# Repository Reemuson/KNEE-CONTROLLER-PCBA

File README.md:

# Boardwright Preview Outputs

Generated from `a710bf6fdfe838f620b5ccc1c5d6b80bbb2f2a4c` on branch `dev`.

Variant: `PRELIMINARY`

This branch is disposable and generated by GitHub Actions. Do not edit
files here by hand.

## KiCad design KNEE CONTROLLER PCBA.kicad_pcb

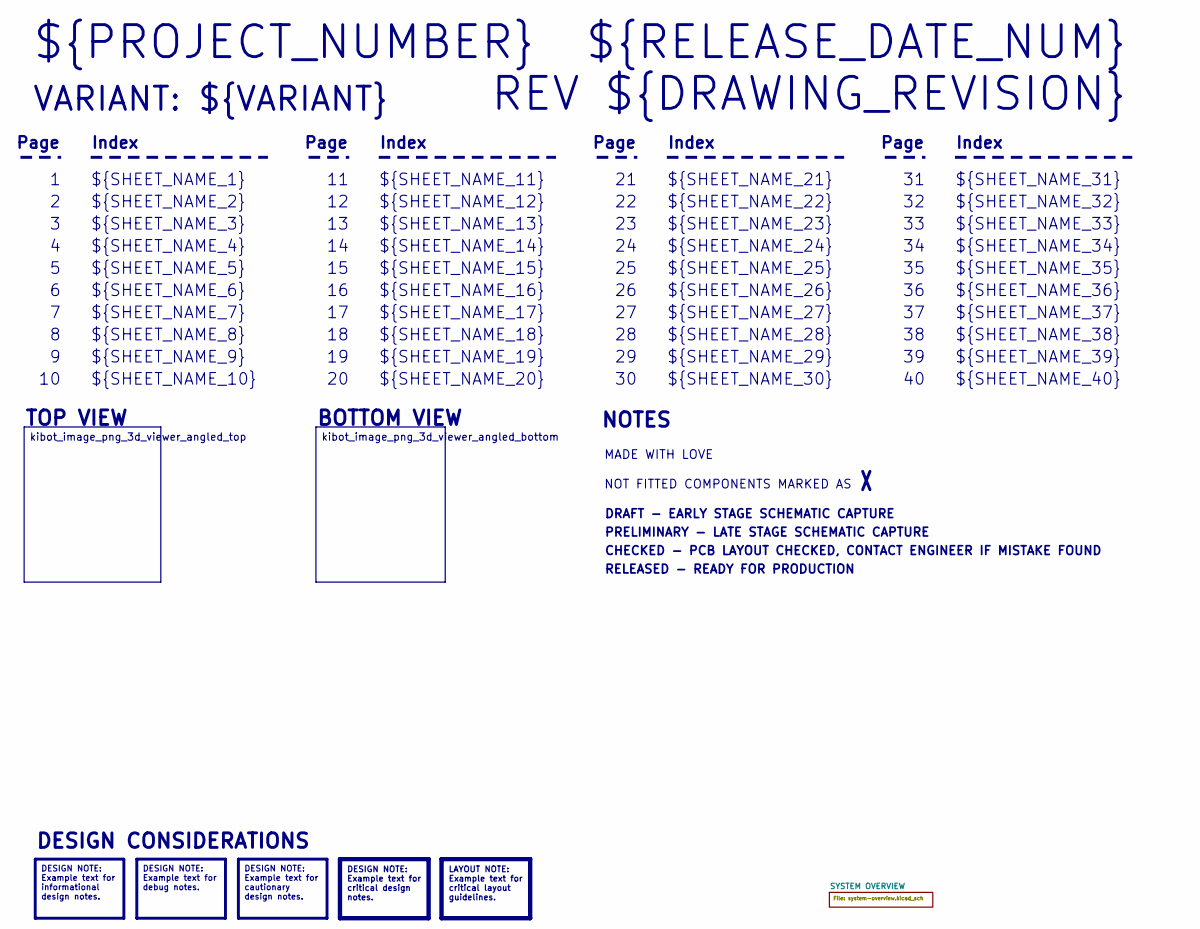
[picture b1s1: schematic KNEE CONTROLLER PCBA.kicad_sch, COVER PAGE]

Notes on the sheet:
VARIANT: ${VARIANT}
RELEASED - READY FOR PRODUCTION
${SHEET_NAME_24}
Index
Page
PRELIMINARY - LATE STAGE SCHEMATIC CAPTURE
${SHEET_NAME_22}
DRAFT - EARLY STAGE SCHEMATIC CAPTURE
${SHEET_NAME_12}
${SHEET_NAME_8}
${SHEET_NAME_2}
${SHEET_NAME_5}
${SHEET_NAME_20}
${SHEET_NAME_23}
${RELEASE_DATE_NUM}
${SHEET_NAME_35}
NOT FITTED COMPONENTS MARKED AS
${SHEET_NAME_11}
${SHEET_NAME_6}
${SHEET_NAME_37}
${SHEET_NAME_26}
${SHEET_NAME_36}
REV ${DRAWING_REVISION}
${SHEET_NAME_15}
CHECKED - PCB LAYOUT CHECKED, CONTACT ENGINEER IF MISTAKE FOUND
BOTTOM VIEW
${SHEET_NAME_14}
${SHEET_NAME_21}
${SHEET_NAME_17}
${SHEET_NAME_18}
${SHEET_NAME_7}
${SHEET_NAME_31}
${PROJECT_NUMBER}
NOTES
${SHEET_NAME_40}
${SHEET_NAME_39}
${SHEET_NAME_32}
${SHEET_NAME_1}
${SHEET_NAME_9}
${SHEET_NAME_38}

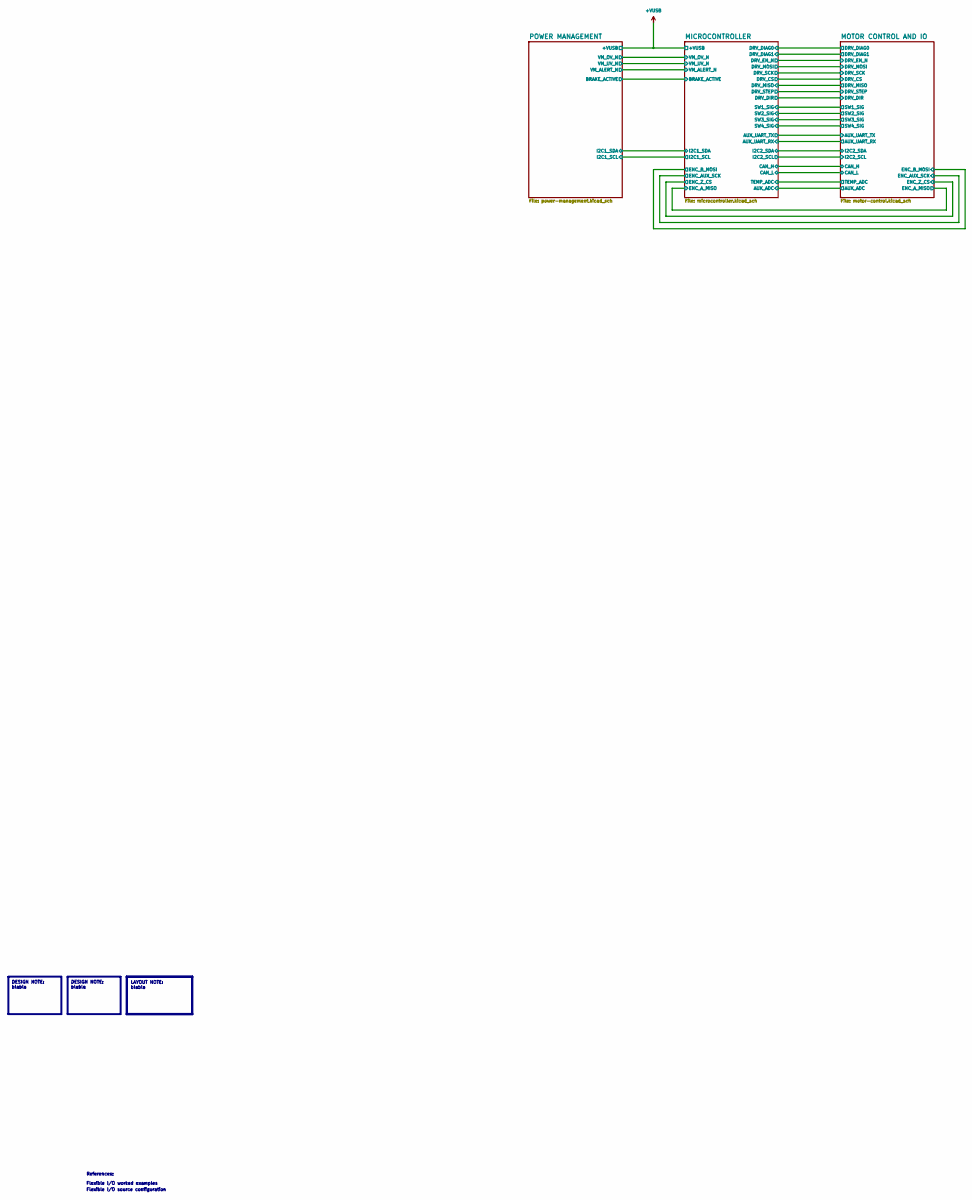
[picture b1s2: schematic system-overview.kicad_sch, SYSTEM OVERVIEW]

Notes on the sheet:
References:
Flexible I/O worked examples
Flexible I/O source configuration
DESIGN NOTE: blabla
LAYOUT NOTE: blabla

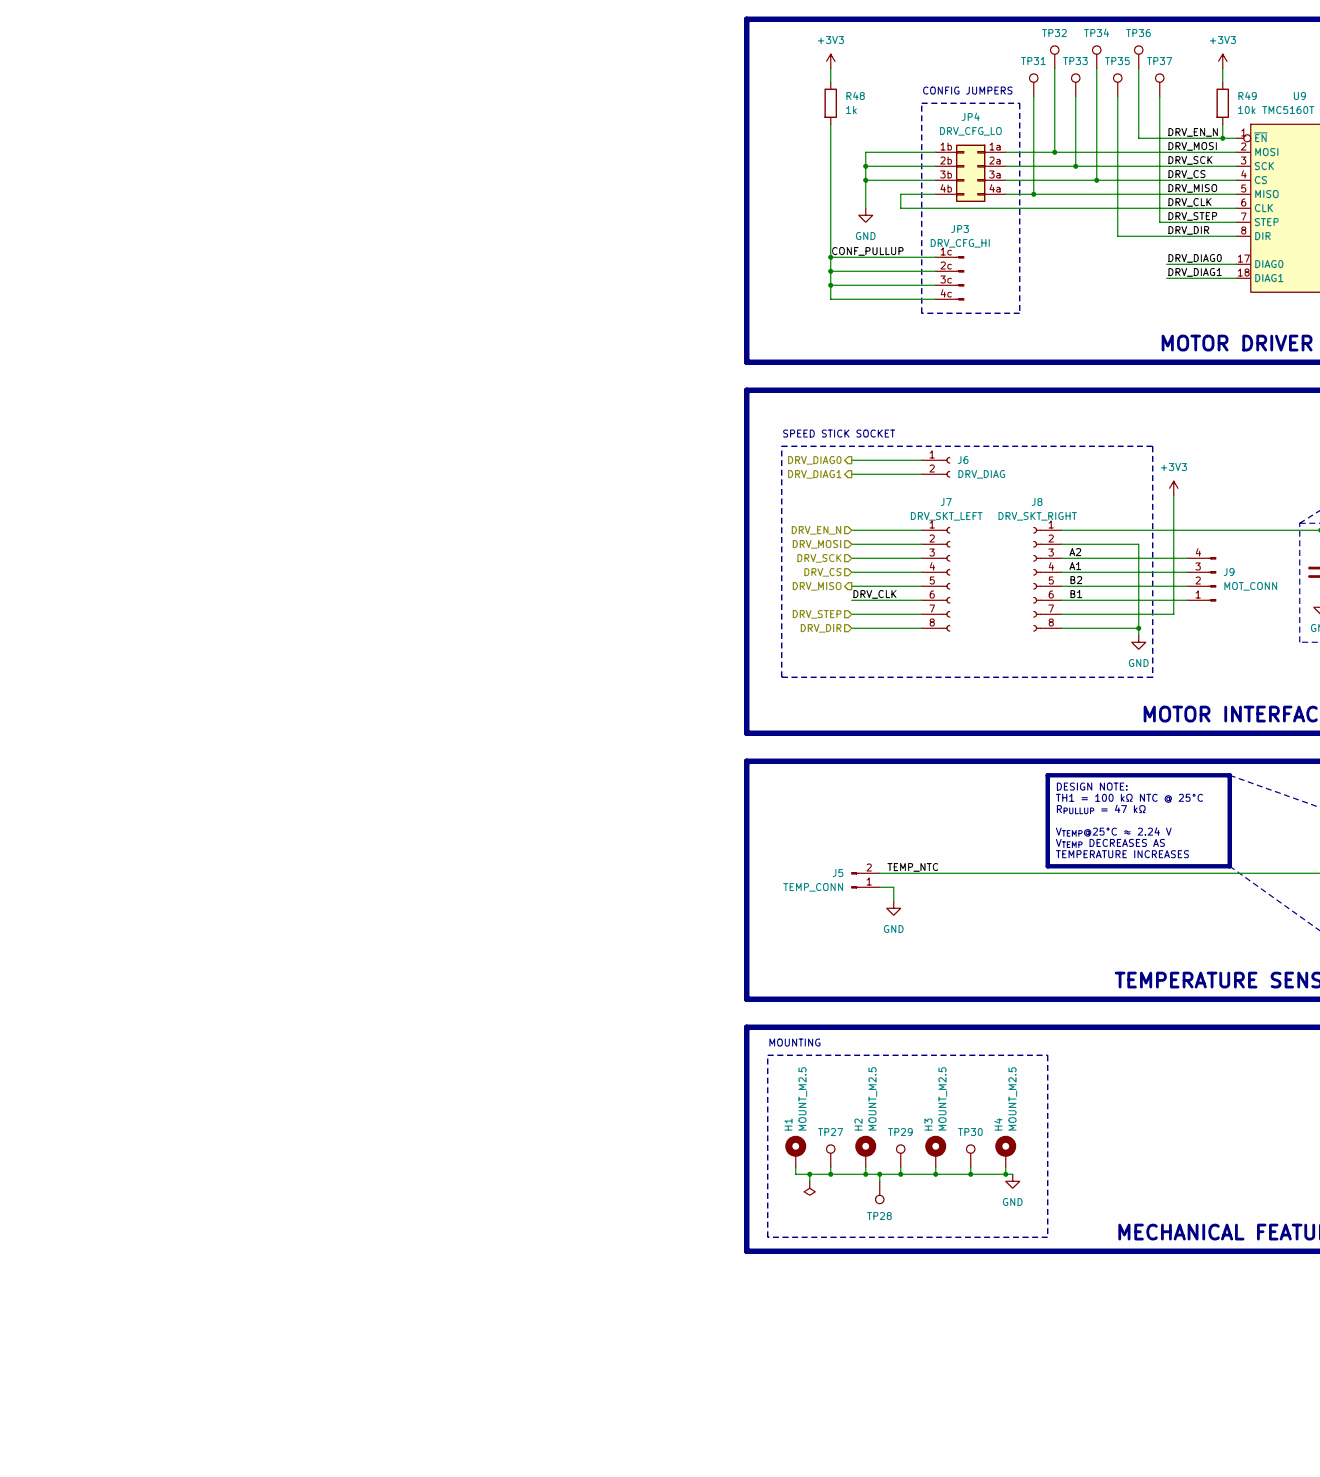
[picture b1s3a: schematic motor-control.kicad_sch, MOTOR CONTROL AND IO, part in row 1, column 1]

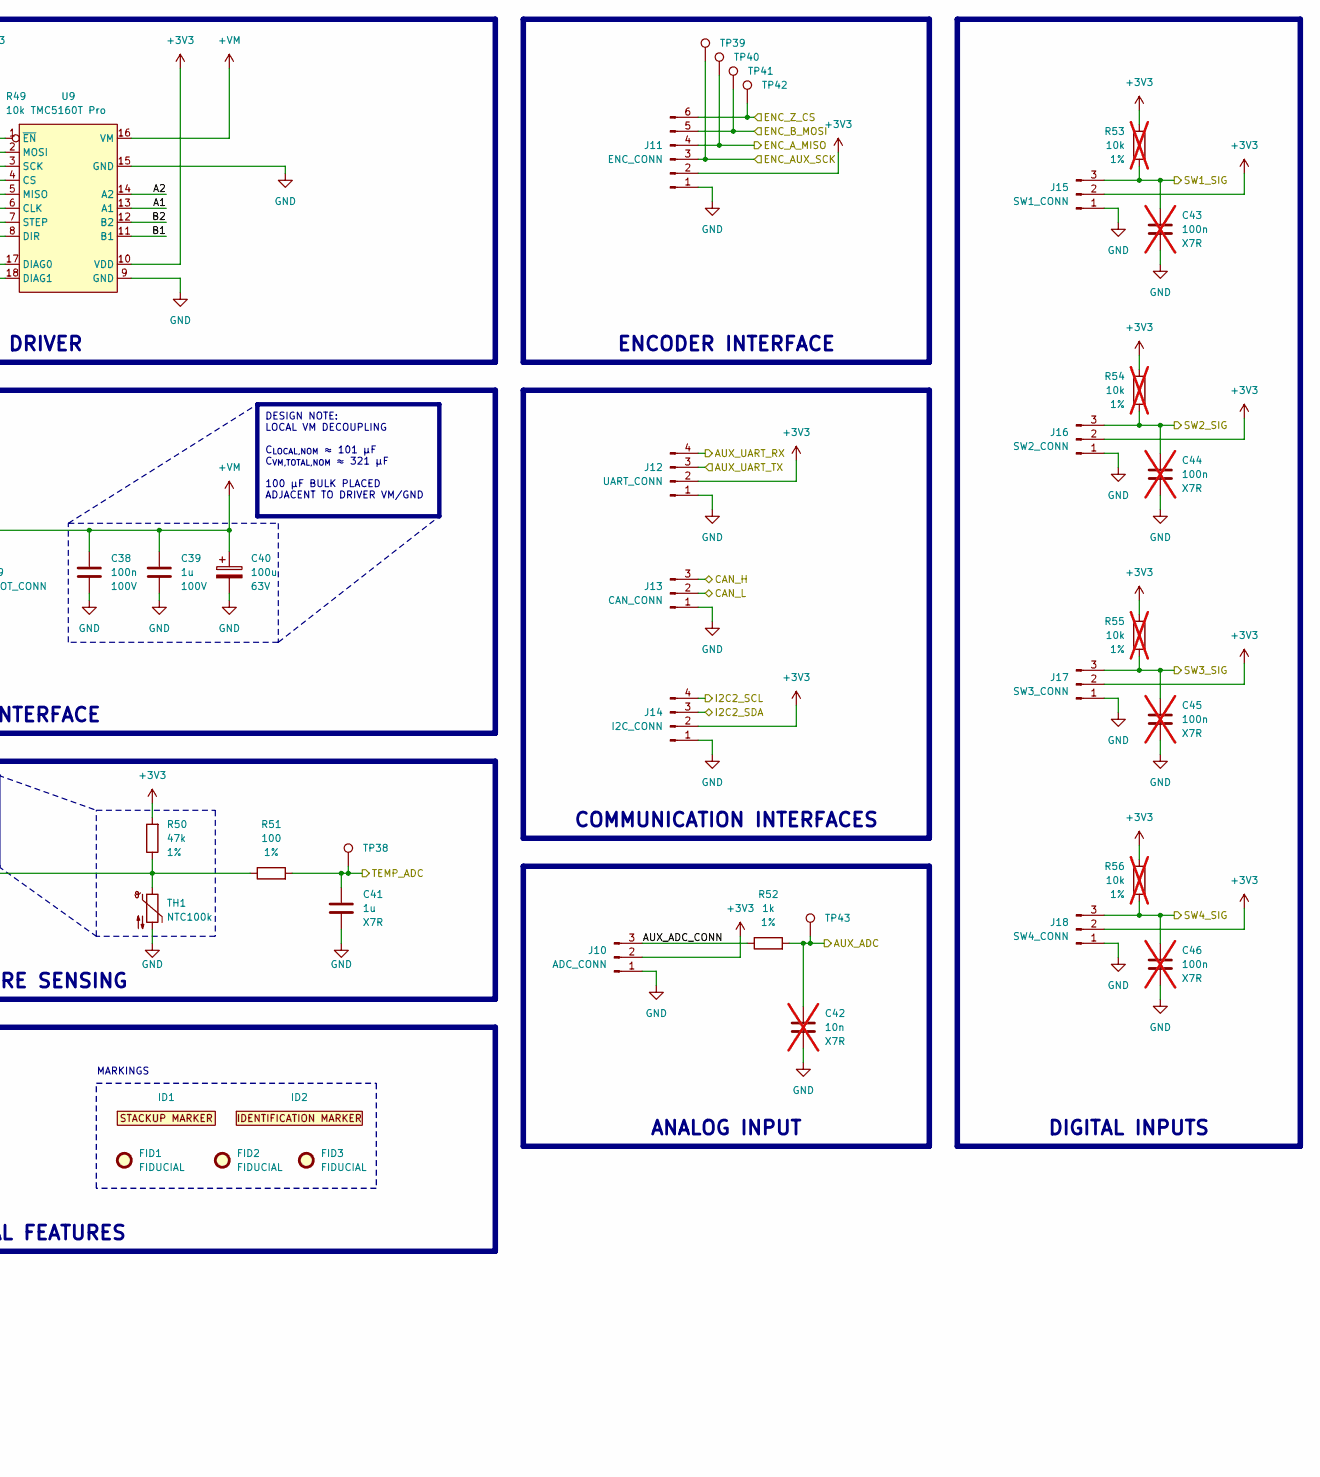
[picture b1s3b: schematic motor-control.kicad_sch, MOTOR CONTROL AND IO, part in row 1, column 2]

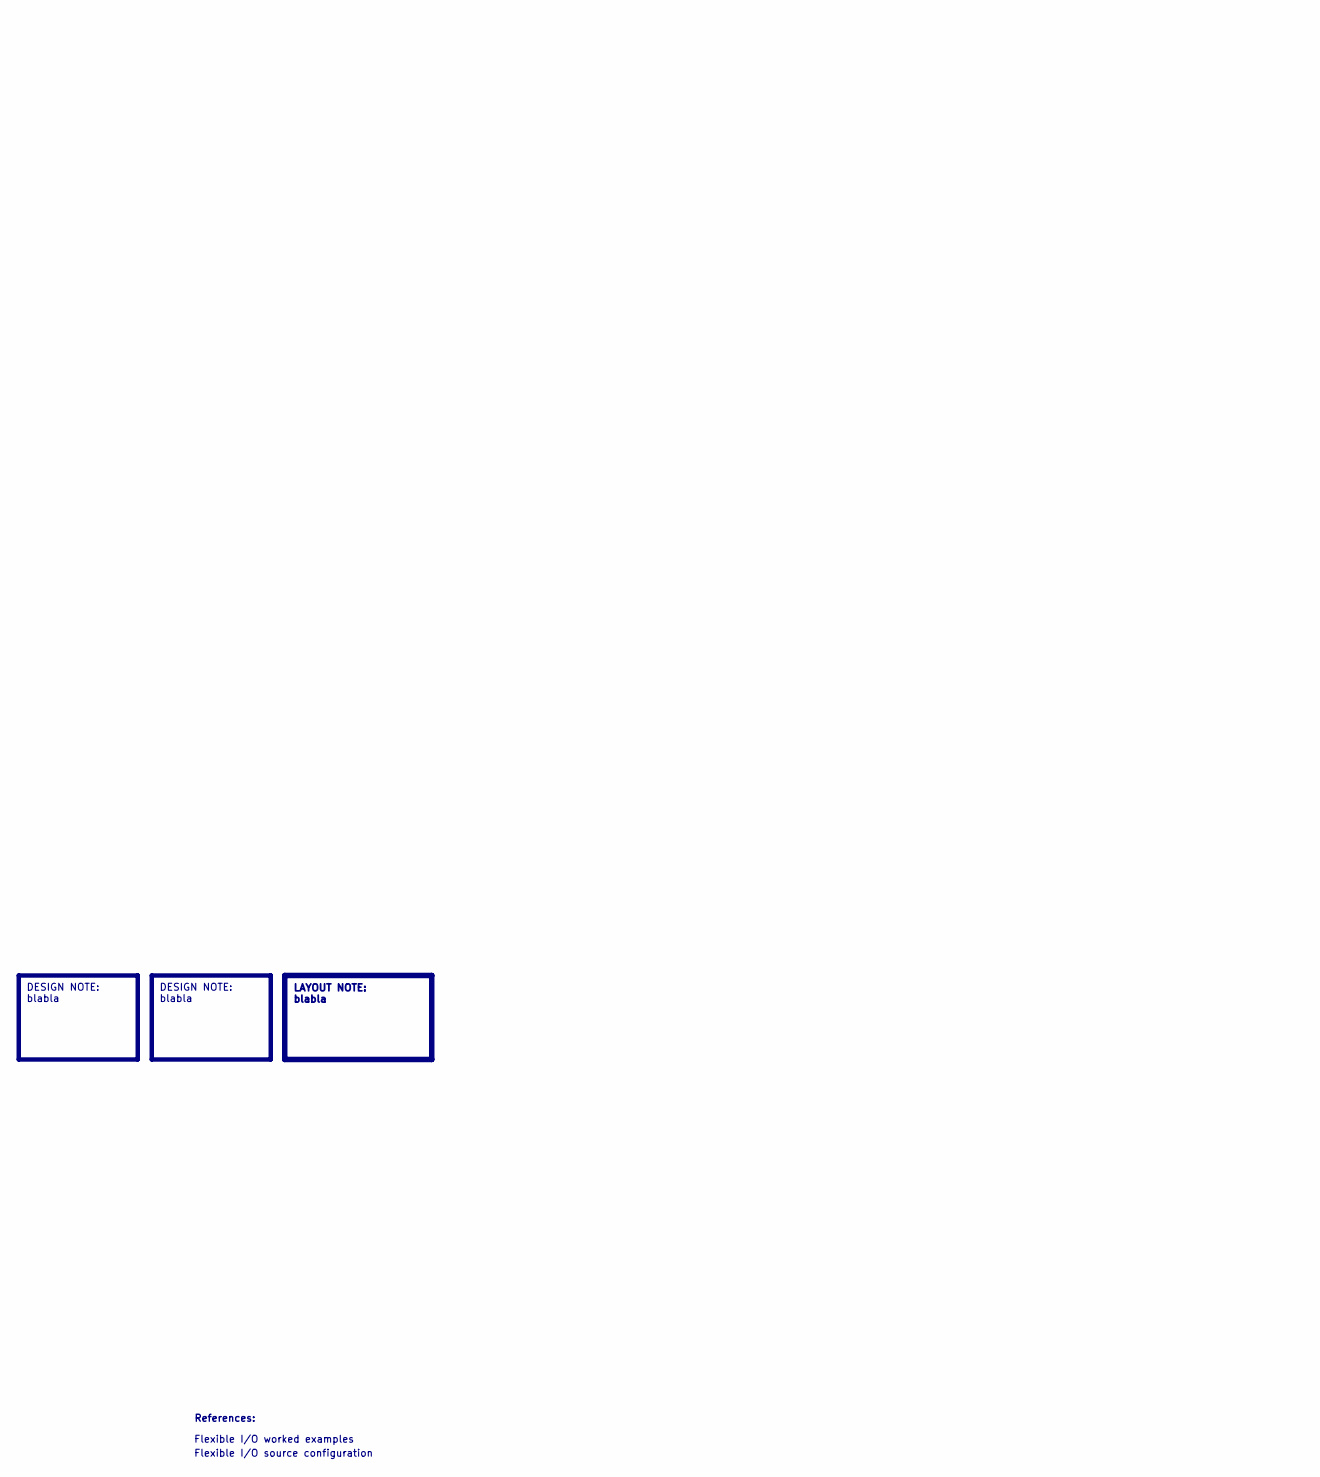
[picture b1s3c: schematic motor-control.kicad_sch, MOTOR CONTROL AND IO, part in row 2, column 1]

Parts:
C38: 100n; C_0603_1608_DensityHigh; Voltage_Rating 100V; Tolerance 10%; MPN CC0603KRX7R0BB104
C39: 1u; C_1206_3216_DensityHigh; Voltage_Rating 100V; Tolerance 10%; MPN CC1206KKX7R0BB105
C40: 100u; CP_Radial_D8.0mm_P3.50mm; Voltage_Rating 63V; Tolerance 20%; MPN 63PX100MEFC8X11.5
C41: 1u; C_0805_2012_DensityHigh; Voltage_Rating 10V; Tolerance 10%; MPN CC0805MKX7R6BB105
C42: 10n; C_0603_1608_DensityHigh; Voltage_Rating 50V; Tolerance 10%; MPN CC0603KRX7R9BB103; not fitted
C43, C44, C45, C46: 100n; C_0603_1608_DensityHigh; Voltage_Rating 50V; Tolerance 10%; MPN CC0603KRX7R9BB104; not fitted
FID1, FID2, FID3: FIDUCIAL; Fiducial_1mm_Mask2mm
H1, H2, H3, H4: MOUNT_M2.5; MountingHole_2.7mm_M2.5_ISO7380_Pad
ID1: BOARD_STACKUP_MARKER; STACKUP_ID_2L
ID2: BOARD_IDENTIFICATION_MARKER; BOARD_IDENTIFICATION
J5: TEMP_CONN; Molex_KK-254_AE-6410-02A_1x02_P2.54mm_Vertical; MPN HM3412
J6: DRV_DIAG; PinSocket_1x02_P2.54mm_Vertical; MPN HX PM2.54-1x2P ZC H11
J7: DRV_SKT_LEFT; PinSocket_1x08_P2.54mm_Vertical; MPN HX PM2.54-1x8P ZC H11
J8: DRV_SKT_RIGHT; PinSocket_1x08_P2.54mm_Vertical; MPN HX PM2.54-1x8P ZC H11
J9: MOT_CONN; Molex_Micro-Fit_3.0_43650-0415_1x04_P3.00mm_Vertical; MPN 0436500415
J10: ADC_CONN; Molex_KK-254_AE-6410-03A_1x03_P2.54mm_Vertical; MPN HM3413
J11: ENC_CONN; Molex_KK-254_AE-6410-06A_1x06_P2.54mm_Vertical; MPN HM3416
J12: UART_CONN; Molex_KK-254_AE-6410-04A_1x04_P2.54mm_Vertical; MPN HM3414
J13: CAN_CONN; Molex_KK-254_AE-6410-03A_1x03_P2.54mm_Vertical; MPN HM3413
J14: I2C_CONN; Molex_KK-254_AE-6410-04A_1x04_P2.54mm_Vertical; MPN HM3414
J15: SW1_CONN; PinHeader_1x03_P2.54mm_Vertical; MPN HM3212
J16: SW2_CONN; PinHeader_1x03_P2.54mm_Vertical; MPN HM3212
J17: SW3_CONN; PinHeader_1x03_P2.54mm_Vertical; MPN HM3212
J18: SW4_CONN; PinHeader_1x03_P2.54mm_Vertical; MPN HM3212
JP3: DRV_CFG_HI; PinHeader_1x04_P2.54mm_Vertical; MPN HM3212
JP4: DRV_CFG_LO; PinHeader_2x04_P2.54mm_Vertical; MPN HM3250
R48, R52: 1k; R_0603_1608_DensityHigh; Tolerance 1%; Voltage_Rating 75V; MPN RT0603FRE071KL
R49: 10k; R_0603_1608_DensityHigh; Tolerance 1%; Voltage_Rating 75V; MPN RT0603FRE1010KL
R50: 47k; R_0603_1608_DensityHigh; Tolerance 1%; Voltage_Rating 75V; MPN RT0603FRE0747KL
R51: 100; R_0603_1608_DensityHigh; Tolerance 1%; Voltage_Rating 75V; MPN RT0603FRE07100RL
R53, R54, R55, R56: 10k; R_0603_1608_DensityHigh; Tolerance 1%; Voltage_Rating 75V; MPN RT0603FRE1010KL; not fitted
TH1: NTC100k
TP27, TP28, TP29, TP30: G; TestPoint_Pad_1.0x1.0mm
TP31: DRV_MISO; TestPoint_Pad_D0.4mm
TP32: DRV_MOSI; TestPoint_Pad_D0.4mm
TP33: DRV_SCK; TestPoint_Pad_D0.4mm
TP34: DRV_CS; TestPoint_Pad_D0.4mm
TP35: DRV_DIR; TestPoint_Pad_D0.4mm
TP36: DRV_EN_N; TestPoint_Pad_D0.4mm
TP37: STEP_DIR; TestPoint_Pad_D0.4mm
TP38: TEMP_ADC; TestPoint_Pad_D0.4mm
TP39: ENC_AUX_SCK; TestPoint_Pad_D0.4mm
TP40: ENC_A_MISO; TestPoint_Pad_D0.4mm
TP41: ENC_B_MOSI; TestPoint_Pad_D0.4mm
TP42: ENC_Z_CS; TestPoint_Pad_D0.4mm
TP43: AUX_ADC; TestPoint_Pad_D0.4mm
U9: TMC5160T Pro; TMC5160T PRO; MPN TMC5160T Pro

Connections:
+3V3: J8.7, J10.2, J11.2, J12.2, J14.2, J15.2, J16.2, J17.2, J18.2, R48.1, R49.1, R50.2, R53.1, R54.1, R55.1, R56.1, U9.10 (VDD); also elsewhere on the board
+VM: C38.1, C39.2, C40.1, J8.1, U9.16 (VM); also elsewhere on the board
/SYSTEM OVERVIEW/MICROCONTROLLER/AUX_ADC: C42.2, R52.2, TP43.1; also elsewhere on the board
/SYSTEM OVERVIEW/MICROCONTROLLER/AUX_UART_RX: J12.4; also elsewhere on the board
/SYSTEM OVERVIEW/MICROCONTROLLER/AUX_UART_TX: J12.3; also elsewhere on the board
/SYSTEM OVERVIEW/MICROCONTROLLER/CAN_H: J13.3; also elsewhere on the board
/SYSTEM OVERVIEW/MICROCONTROLLER/CAN_L: J13.2; also elsewhere on the board
/SYSTEM OVERVIEW/MICROCONTROLLER/ENC_AUX_SCK: J11.3, TP39.1; also elsewhere on the board
/SYSTEM OVERVIEW/MICROCONTROLLER/ENC_A_MISO: J11.4, TP40.1; also elsewhere on the board
/SYSTEM OVERVIEW/MICROCONTROLLER/ENC_B_MOSI: J11.5, TP41.1; also elsewhere on the board
/SYSTEM OVERVIEW/MICROCONTROLLER/ENC_Z_CS: J11.6, TP42.1; also elsewhere on the board
/SYSTEM OVERVIEW/MICROCONTROLLER/I2C2_SCL: J14.4; also elsewhere on the board
/SYSTEM OVERVIEW/MICROCONTROLLER/I2C2_SDA: J14.3; also elsewhere on the board
/SYSTEM OVERVIEW/MICROCONTROLLER/SW1_SIG: C43.2, J15.3, R53.2; also elsewhere on the board
/SYSTEM OVERVIEW/MICROCONTROLLER/SW2_SIG: C44.2, J16.3, R54.2; also elsewhere on the board
/SYSTEM OVERVIEW/MICROCONTROLLER/SW3_SIG: C45.2, J17.3, R55.2; also elsewhere on the board
/SYSTEM OVERVIEW/MICROCONTROLLER/SW4_SIG: C46.2, J18.3, R56.2; also elsewhere on the board
/SYSTEM OVERVIEW/MICROCONTROLLER/TEMP_ADC: C41.2, R51.2, TP38.1; also elsewhere on the board
/SYSTEM OVERVIEW/MOTOR CONTROL AND IO/A1: J8.4, J9.3, U9.13 (A1)
/SYSTEM OVERVIEW/MOTOR CONTROL AND IO/A2: J8.3, J9.4, U9.14 (A2)
/SYSTEM OVERVIEW/MOTOR CONTROL AND IO/AUX_ADC_CONN: J10.3, R52.1
/SYSTEM OVERVIEW/MOTOR CONTROL AND IO/B1: J8.6, J9.1, U9.11 (B1)
/SYSTEM OVERVIEW/MOTOR CONTROL AND IO/B2: J8.5, J9.2, U9.12 (B2)
/SYSTEM OVERVIEW/MOTOR CONTROL AND IO/CONF_PULLUP: JP3.1c (Pin_1), JP3.2c (Pin_2), JP3.3c (Pin_3), JP3.4c (Pin_4), R48.2
/SYSTEM OVERVIEW/MOTOR CONTROL AND IO/DRV_CLK: J7.6, JP4.4b, U9.6 (CLK)
/SYSTEM OVERVIEW/MOTOR CONTROL AND IO/DRV_CS: J7.4, JP4.3a, TP34.1, U9.4 (CS); also elsewhere on the board
/SYSTEM OVERVIEW/MOTOR CONTROL AND IO/DRV_DIAG0: J6.1; also elsewhere on the board
/SYSTEM OVERVIEW/MOTOR CONTROL AND IO/DRV_DIAG1: J6.2; also elsewhere on the board
/SYSTEM OVERVIEW/MOTOR CONTROL AND IO/DRV_DIR: J7.8, TP35.1, U9.8 (DIR); also elsewhere on the board
/SYSTEM OVERVIEW/MOTOR CONTROL AND IO/DRV_EN_N: J7.1, R49.2, TP36.1, U9.1 (~EN); also elsewhere on the board
/SYSTEM OVERVIEW/MOTOR CONTROL AND IO/DRV_MISO: J7.5, JP4.4a, TP31.1, U9.5 (MISO); also elsewhere on the board
/SYSTEM OVERVIEW/MOTOR CONTROL AND IO/DRV_MOSI: J7.2, JP4.1a, TP32.1, U9.2 (MOSI); also elsewhere on the board
/SYSTEM OVERVIEW/MOTOR CONTROL AND IO/DRV_SCK: J7.3, JP4.2a, TP33.1, U9.3 (SCK); also elsewhere on the board
/SYSTEM OVERVIEW/MOTOR CONTROL AND IO/DRV_STEP: J7.7, TP37.1, U9.7 (STEP); also elsewhere on the board
/SYSTEM OVERVIEW/MOTOR CONTROL AND IO/TEMP_NTC: J5.2, R50.1, R51.1, TH1.1
GND: C38.2, C39.1, C40.2, C41.1, C42.1, C43.1, C44.1, C45.1, C46.1, H1.1, H2.1, H3.1, H4.1, J5.1, J8.2, J8.8, J10.1, J11.1, J12.1, J13.1, J14.1, J15.1, J16.1, J17.1, J18.1, JP4.1b, JP4.2b, JP4.3b, TH1.2, TP27.1, TP28.1, TP29.1, TP30.1, U9.9 (GND), U9.15 (GND); also elsewhere on the board

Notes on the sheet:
SPEED STICK SOCKET
References:
MARKINGS
CONFIG JUMPERS
Flexible I/O worked examples
Flexible I/O source configuration
MOUNTING
MOTOR DRIVER
DESIGN NOTE: blabla
LAYOUT NOTE: blabla
DESIGN NOTE: TH1 = 100 kΩ NTC @ 25°C R_{PULLUP} = 47 kΩ V_{TEMP}@25°C ≈ 2.24 V V_{TEMP} DECREASES AS TEMPERATURE INCREASES
DIGITAL INPUTS
ANALOG INPUT
COMMUNICATION INTERFACES
TEMPERATURE SENSING
MOTOR INTERFACE
MECHANICAL FEATURES
ENCODER INTERFACE
DESIGN NOTE: LOCAL VM DECOUPLING C_{LOCAL,NOM} ≈ 101 µF C_{VM,TOTAL,NOM} ≈ 321 µF 100 µF BULK PLACED ADJACENT TO DRIVER VM/GND

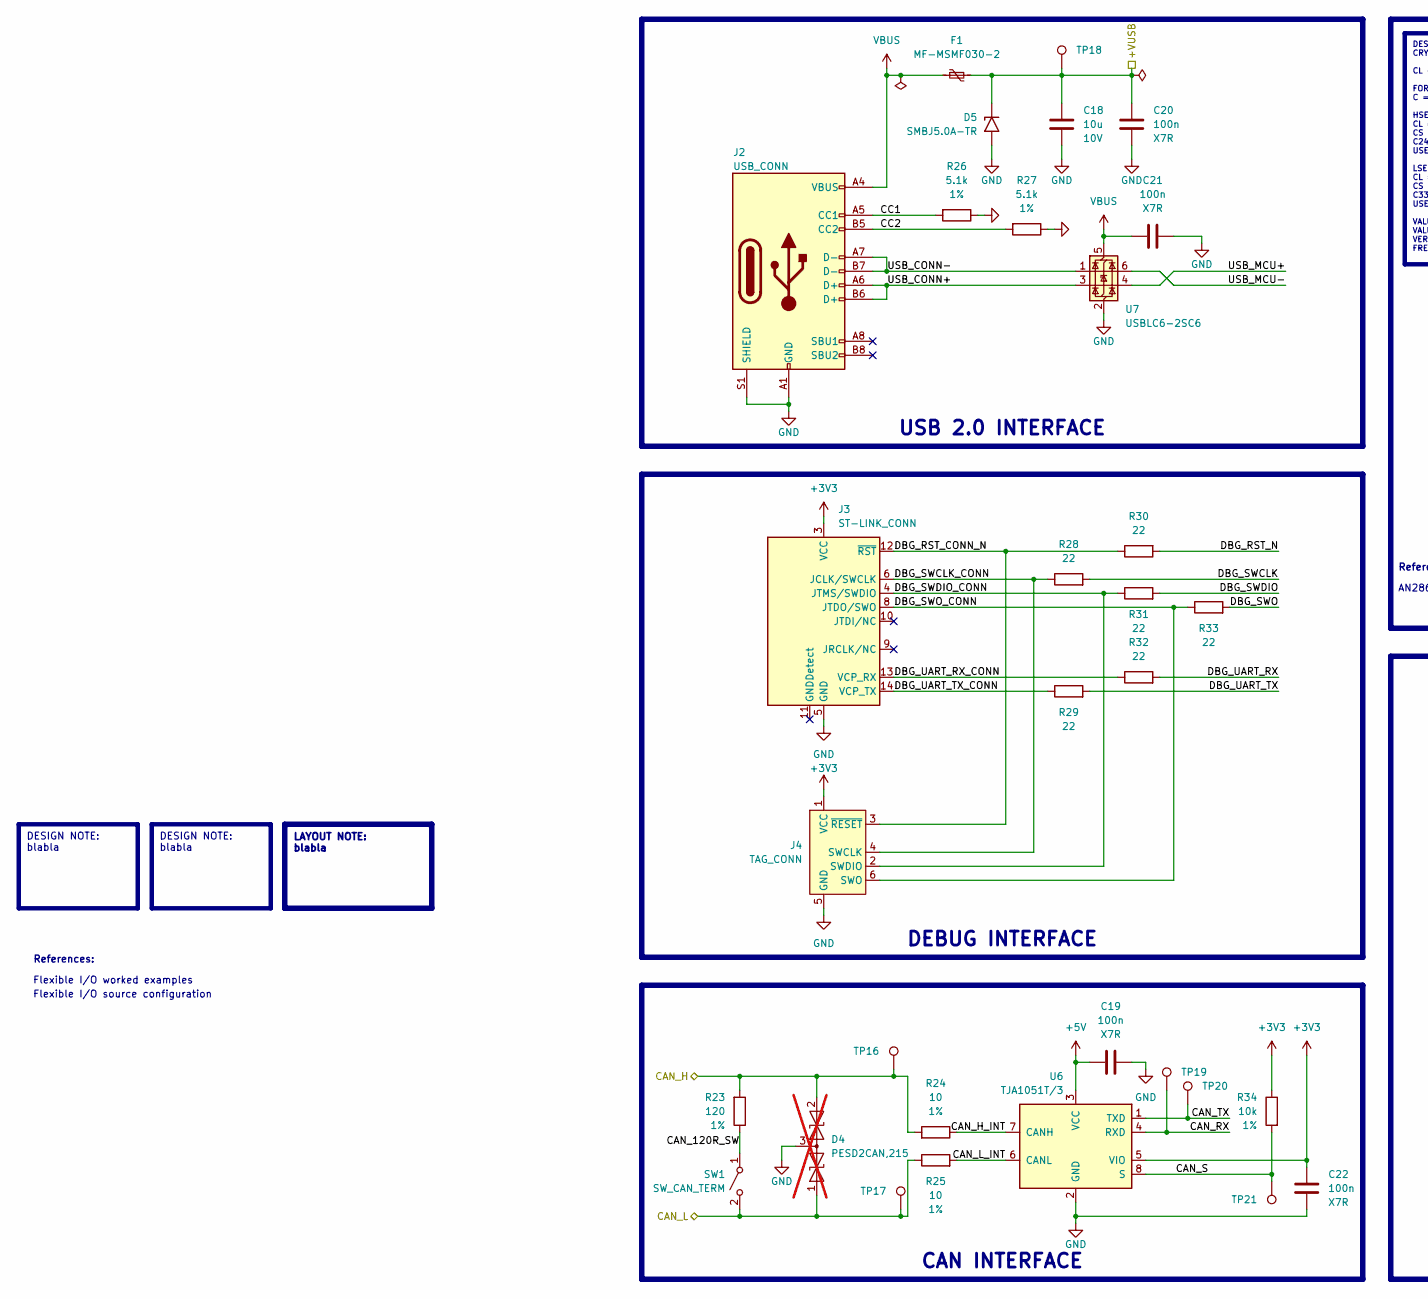
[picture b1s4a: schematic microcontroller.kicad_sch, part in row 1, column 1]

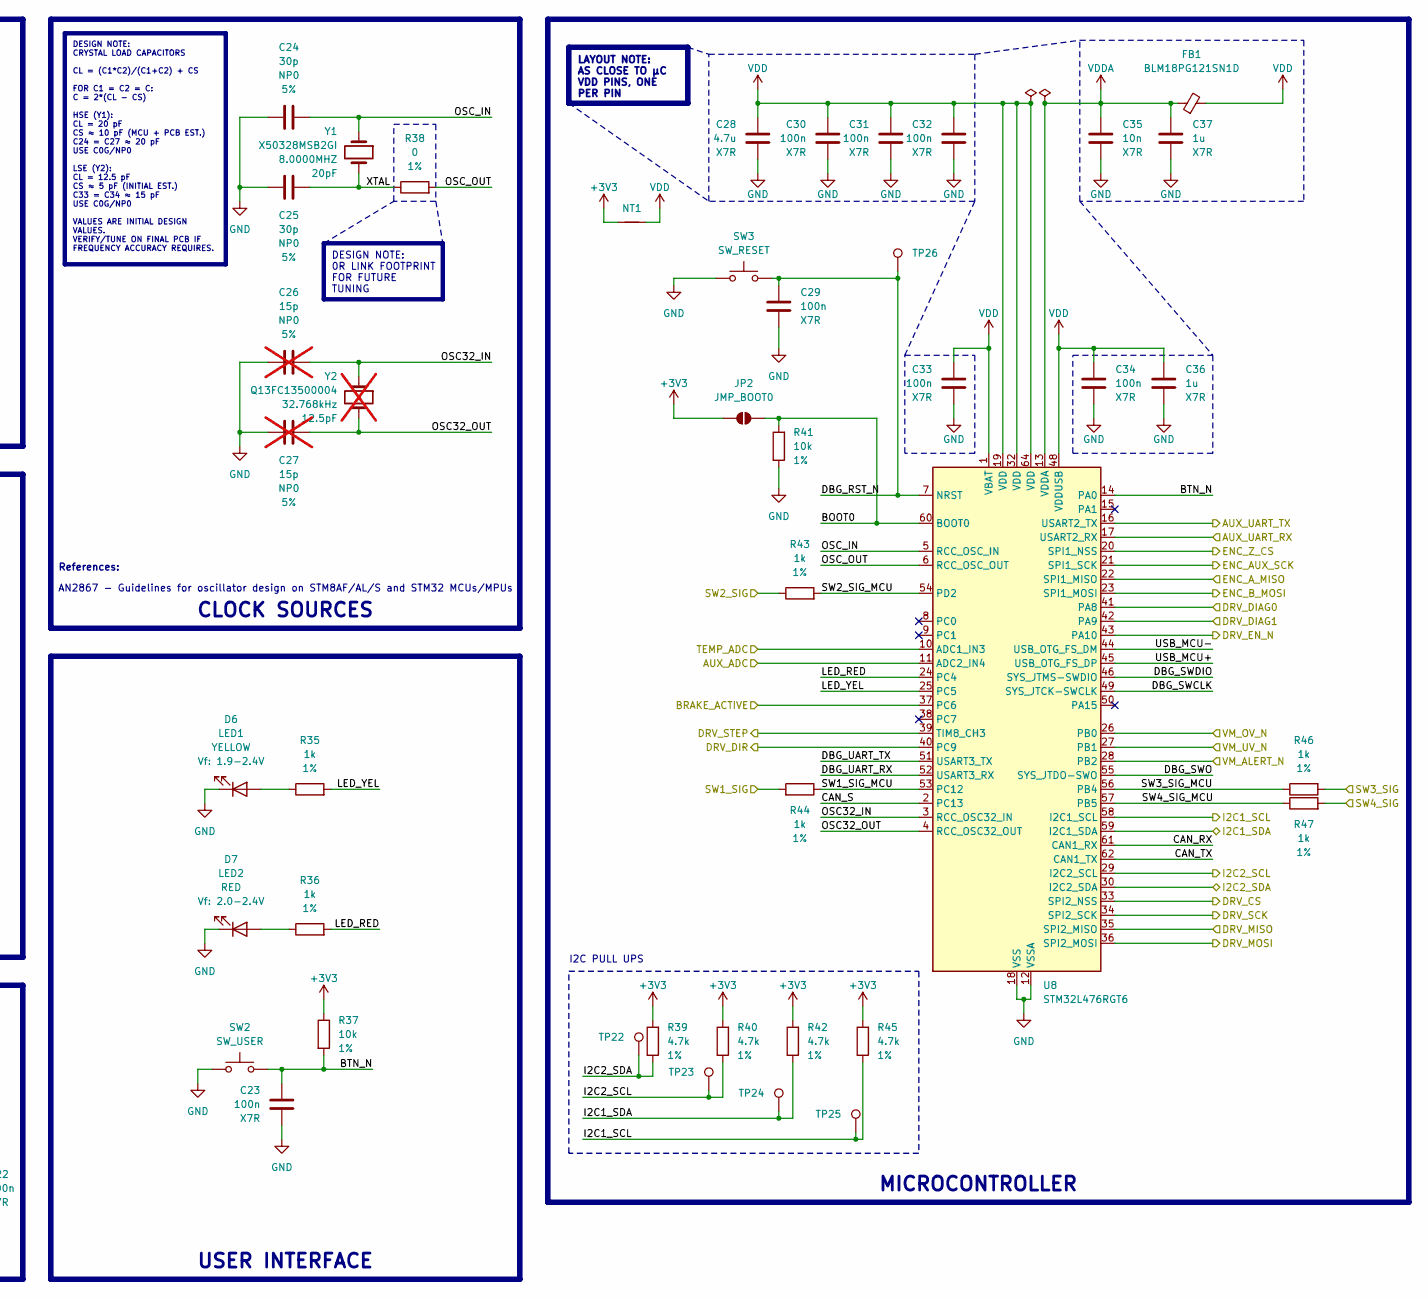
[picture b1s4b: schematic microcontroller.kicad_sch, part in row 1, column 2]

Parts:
C18: 10u; C_0805_2012_DensityHigh; Voltage_Rating 10V; Tolerance 10%; MPN CC0805KFX7R6BB106
C19, C20, C21, C22, C23, C29, C30, C31, C32, C33, C34: 100n; C_0603_1608_DensityHigh; Voltage_Rating 50V; Tolerance 10%; MPN CC0603KRX7R9BB104
C24, C25: 30p; C_0603_1608_DensityHigh; Voltage_Rating 50V; Tolerance 5%; MPN CC0603JRNPO9BN300
C26, C27: 15p; C_0402_1005_DensityHigh; Voltage_Rating 50V; Tolerance 5%; MPN CC0402JRNPO9BN150; not fitted
C28: 4.7u; C_1206_3216_DensityHigh; Voltage_Rating 50V; Tolerance 10%; MPN CC1206KFX7R9BB475
C35: 10n; C_0603_1608_DensityHigh; Voltage_Rating 50V; Tolerance 10%; MPN CC0603KRX7R9BB103
C36, C37: 1u; C_0805_2012_DensityHigh; Voltage_Rating 10V; Tolerance 10%; MPN CC0805MKX7R6BB105
D4: PESD2CAN,215; SOT-23; MPN PESD2CAN,215; not fitted
D5: SMBJ5.0A-TR; D_SMB; MPN SMBJ5.0A-TR
D6: LED1; LED_0805_2012_DensityHigh; MPN LTST-C171YKT
D7: LED2; LED_0805_2012_DensityHigh; MPN LTST-C171KRKT
F1: MF-MSMF030-2; R_1812_4532Metric; Voltage_Rating 30V; MPN MF-MSMF030-2
FB1: BLM18PG121SN1D; R_0603_1608_DensityHigh; MPN BLM18PG121SN1D
J2: USB_CONN; USB_C_Receptacle_HCTL_HC-TYPE-C-16P-01A; MPN USB4105-GF-A
J3: ST-LINK_CONN; PinHeader_2x07_P1.27mm_Vertical_SMD; MPN 20021121-00014T1LF
J4: TAG_CONN; Tag-Connect_TC2030-IDC-NL_2x03_P1.27mm_Vertical
JP2: JMP_BOOT0; SolderJumper-2_P1.3mm_Open_TrianglePad1.0x1.5mm
NT1: NetTie_2; NetTie-2_SMD_Pad0.5mm
R23: 120; R_0603_1608_DensityHigh; Tolerance 1%; Voltage_Rating 75V; MPN RT0603FRE07120RL
R24, R25: 10; R_0603_1608_DensityHigh; Tolerance 1%; Voltage_Rating 75V; MPN RT0603FRE1310RL
R26, R27: 5.1k; R_0603_1608_DensityHigh; Tolerance 1%; Voltage_Rating 75V; MPN RT0603FRD075K1L
R28, R29, R30, R31, R33: 22; R_0603_1608_DensityHigh; Tolerance 1%; Voltage_Rating 75V; MPN RT0603FRE0722RL
R32: 22; R_0603_1608_DensityLow; Tolerance 1%; Voltage_Rating 75V; MPN RT0603FRE0722RL
R34, R37, R41: 10k; R_0603_1608_DensityHigh; Tolerance 1%; Voltage_Rating 75V; MPN RT0603FRE1010KL
R35, R36, R43, R44, R46, R47: 1k; R_0603_1608_DensityHigh; Tolerance 1%; Voltage_Rating 75V; MPN RT0603FRE071KL
R38: 0; R_0402_1005_DensityHigh; Tolerance 1%; Voltage_Rating 75V; MPN RC0402JR-070RP
R39, R40, R42, R45: 4.7k; R_0603_1608_DensityHigh; Tolerance 1%; Voltage_Rating 75V; MPN RT0603FRE074K7L
SW1: SW_CAN_TERM; SW_DIP_SPSTx01_Slide_6.7x4.1mm_W7.62mm_P2.54mm_LowProfile; Voltage_Rating 24V; MPN DS01-254-L-01BE
SW2: SW_USER; SW_SPST_PTS526xxxSMTR; MPN PTS526SK15SMTR2 LFS
SW3: SW_RESET; SW_SPST_PTS526xxxSMTR; MPN PTS526SK15SMTR2 LFS
TP16: CAN_H; TestPoint_Pad_D0.4mm
TP17: CAN_L; TestPoint_Pad_D0.4mm
TP18: +VUSB; TestPoint_Pad_D1.0mm
TP19: CAN_RX; TestPoint_Pad_D0.4mm
TP20: CAN _TX; TestPoint_Pad_D0.4mm
TP21: CAN_S; TestPoint_Pad_D0.4mm
TP22: I2C2_SDA; TestPoint_Pad_D0.4mm
TP23: I2C2_SCL; TestPoint_Pad_D0.4mm
TP24: I2C1_SDA; TestPoint_Pad_D0.4mm
TP25: I2C1_SCL; TestPoint_Pad_D0.4mm
TP26: DBG_RST_N; TestPoint_Pad_D0.4mm
U6: TJA1051T/3; SOIC-8_3.9x4.9mm_P1.27mm; MPN TJA1051T/3,118
U7: USBLC6-2SC6; SOT-23-6; MPN USBLC6-2SC6
U8: STM32L476RGT6; LQFP-64_10x10mm_P0.5mm; MPN STM32L476RGT6
Y1: X50328MSB2GI; Crystal_SMD_5032-2Pin_5.0x3.2mm; MPN ECS-80-18-30-JGN-TR
Y2: Q13FC13500004; Crystal_SMD_3215-2Pin_3.2x1.5mm; MPN ECS-.327-12.5-34B-TR; not fitted

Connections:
+3V3: C22.2, J3.3 (VCC), J4.1 (VCC), JP2.1 (A), NT1.1, R34.1, R37.1, R39.2, R40.2, R42.2, R45.2, U6.5 (VIO); also elsewhere on the board
+5V: C19.2, U6.3 (VCC); also elsewhere on the board
+VUSB: C18.2, C20.1, D5.1 (A1), F1.2, TP18.1; also elsewhere on the board
/SYSTEM OVERVIEW/MICROCONTROLLER/AUX_ADC: U8.11 (ADC2_IN4); also elsewhere on the board
/SYSTEM OVERVIEW/MICROCONTROLLER/AUX_UART_RX: U8.17 (USART2_RX); also elsewhere on the board
/SYSTEM OVERVIEW/MICROCONTROLLER/AUX_UART_TX: U8.16 (USART2_TX); also elsewhere on the board
/SYSTEM OVERVIEW/MICROCONTROLLER/BOOT0: JP2.2 (B), R41.2, U8.60 (BOOT0)
/SYSTEM OVERVIEW/MICROCONTROLLER/BRAKE_ACTIVE: U8.37 (PC6); also elsewhere on the board
/SYSTEM OVERVIEW/MICROCONTROLLER/BTN_N: C23.2, R37.2, SW2.2, U8.14 (PA0)
/SYSTEM OVERVIEW/MICROCONTROLLER/CAN_120R_SW: R23.1, SW1.1 (A)
/SYSTEM OVERVIEW/MICROCONTROLLER/CAN_H: D4.2 (A2), R23.2, R24.2, TP16.1; also elsewhere on the board
/SYSTEM OVERVIEW/MICROCONTROLLER/CAN_H_INT: R24.1, U6.7 (CANH)
/SYSTEM OVERVIEW/MICROCONTROLLER/CAN_L: D4.1 (A1), R25.1, SW1.2 (B), TP17.1; also elsewhere on the board
/SYSTEM OVERVIEW/MICROCONTROLLER/CAN_L_INT: R25.2, U6.6 (CANL)
/SYSTEM OVERVIEW/MICROCONTROLLER/CAN_RX: TP19.1, U6.4 (RXD), U8.61 (CAN1_RX)
/SYSTEM OVERVIEW/MICROCONTROLLER/CAN_S: R34.2, TP21.1, U6.8 (S), U8.2 (PC13)
/SYSTEM OVERVIEW/MICROCONTROLLER/CAN_TX: TP20.1, U6.1 (TXD), U8.62 (CAN1_TX)
/SYSTEM OVERVIEW/MICROCONTROLLER/CC1: J2.A5 (CC1), R26.2
/SYSTEM OVERVIEW/MICROCONTROLLER/CC2: J2.B5 (CC2), R27.2
/SYSTEM OVERVIEW/MICROCONTROLLER/DBG_RST_CONN_N: J3.12 (~RST), J4.3 (~RESET), R30.1
/SYSTEM OVERVIEW/MICROCONTROLLER/DBG_RST_N: C29.1, R30.2, SW3.2, TP26.1, U8.7 (NRST)
/SYSTEM OVERVIEW/MICROCONTROLLER/DBG_SWCLK: R28.2, U8.49 (SYS_JTCK-SWCLK)
/SYSTEM OVERVIEW/MICROCONTROLLER/DBG_SWCLK_CONN: J3.6 (JCLK/SWCLK), J4.4 (SWCLK), R28.1
/SYSTEM OVERVIEW/MICROCONTROLLER/DBG_SWDIO: R31.2, U8.46 (SYS_JTMS-SWDIO)
/SYSTEM OVERVIEW/MICROCONTROLLER/DBG_SWDIO_CONN: J3.4 (JTMS/SWDIO), J4.2 (SWDIO), R31.1
/SYSTEM OVERVIEW/MICROCONTROLLER/DBG_SWO: R33.2, U8.55 (SYS_JTDO-SWO)
/SYSTEM OVERVIEW/MICROCONTROLLER/DBG_SWO_CONN: J3.8 (JTDO/SWO), J4.6 (SWO), R33.1
/SYSTEM OVERVIEW/MICROCONTROLLER/DBG_UART_RX: R32.2, U8.52 (USART3_RX)
/SYSTEM OVERVIEW/MICROCONTROLLER/DBG_UART_RX_CONN: J3.13 (VCP_RX), R32.1
/SYSTEM OVERVIEW/MICROCONTROLLER/DBG_UART_TX: R29.2, U8.51 (USART3_TX)
/SYSTEM OVERVIEW/MICROCONTROLLER/DBG_UART_TX_CONN: J3.14 (VCP_TX), R29.1
/SYSTEM OVERVIEW/MICROCONTROLLER/ENC_AUX_SCK: U8.21 (SPI1_SCK); also elsewhere on the board
/SYSTEM OVERVIEW/MICROCONTROLLER/ENC_A_MISO: U8.22 (SPI1_MISO); also elsewhere on the board
/SYSTEM OVERVIEW/MICROCONTROLLER/ENC_B_MOSI: U8.23 (SPI1_MOSI); also elsewhere on the board
/SYSTEM OVERVIEW/MICROCONTROLLER/ENC_Z_CS: U8.20 (SPI1_NSS); also elsewhere on the board
/SYSTEM OVERVIEW/MICROCONTROLLER/I2C1_SCL: R45.1, TP25.1, U8.58 (I2C1_SCL); also elsewhere on the board
/SYSTEM OVERVIEW/MICROCONTROLLER/I2C1_SDA: R42.1, TP24.1, U8.59 (I2C1_SDA); also elsewhere on the board
/SYSTEM OVERVIEW/MICROCONTROLLER/I2C2_SCL: R40.1, TP23.1, U8.29 (I2C2_SCL); also elsewhere on the board
/SYSTEM OVERVIEW/MICROCONTROLLER/I2C2_SDA: R39.1, TP22.1, U8.30 (I2C2_SDA); also elsewhere on the board
/SYSTEM OVERVIEW/MICROCONTROLLER/LED_RED: R36.2, U8.24 (PC4)
/SYSTEM OVERVIEW/MICROCONTROLLER/LED_YEL: R35.2, U8.25 (PC5)
/SYSTEM OVERVIEW/MICROCONTROLLER/OSC32_IN: C26.2, U8.3 (RCC_OSC32_IN), Y2.1
/SYSTEM OVERVIEW/MICROCONTROLLER/OSC32_OUT: C27.2, U8.4 (RCC_OSC32_OUT), Y2.2
/SYSTEM OVERVIEW/MICROCONTROLLER/OSC_IN: C24.2, U8.5 (RCC_OSC_IN), Y1.1
/SYSTEM OVERVIEW/MICROCONTROLLER/OSC_OUT: R38.2, U8.6 (RCC_OSC_OUT)
/SYSTEM OVERVIEW/MICROCONTROLLER/SW1_SIG: R44.2; also elsewhere on the board
/SYSTEM OVERVIEW/MICROCONTROLLER/SW1_SIG_MCU: R44.1, U8.53 (PC12)
/SYSTEM OVERVIEW/MICROCONTROLLER/SW2_SIG: R43.1; also elsewhere on the board
/SYSTEM OVERVIEW/MICROCONTROLLER/SW2_SIG_MCU: R43.2, U8.54 (PD2)
/SYSTEM OVERVIEW/MICROCONTROLLER/SW3_SIG: R46.2; also elsewhere on the board
/SYSTEM OVERVIEW/MICROCONTROLLER/SW3_SIG_MCU: R46.1, U8.56 (PB4)
/SYSTEM OVERVIEW/MICROCONTROLLER/SW4_SIG: R47.2; also elsewhere on the board
/SYSTEM OVERVIEW/MICROCONTROLLER/SW4_SIG_MCU: R47.1, U8.57 (PB5)
/SYSTEM OVERVIEW/MICROCONTROLLER/TEMP_ADC: U8.10 (ADC1_IN3); also elsewhere on the board
/SYSTEM OVERVIEW/MICROCONTROLLER/USB_CONN+: J2.A6 (D+), J2.B6 (D+), U7.3 (I/O2)
/SYSTEM OVERVIEW/MICROCONTROLLER/USB_CONN-: J2.A7 (D-), J2.B7 (D-), U7.1 (I/O1)
/SYSTEM OVERVIEW/MICROCONTROLLER/USB_MCU+: U7.4 (I/O2), U8.45 (USB_OTG_FS_DP)
/SYSTEM OVERVIEW/MICROCONTROLLER/USB_MCU-: U7.6 (I/O1), U8.44 (USB_OTG_FS_DM)
/SYSTEM OVERVIEW/MICROCONTROLLER/VM_ALERT_N: U8.28 (PB2); also elsewhere on the board
/SYSTEM OVERVIEW/MICROCONTROLLER/VM_OV_N: U8.26 (PB0); also elsewhere on the board
/SYSTEM OVERVIEW/MICROCONTROLLER/VM_UV_N: U8.27 (PB1); also elsewhere on the board
/SYSTEM OVERVIEW/MICROCONTROLLER/XTAL: C25.2, R38.1, Y1.2
/SYSTEM OVERVIEW/MOTOR CONTROL AND IO/DRV_CS: U8.33 (SPI2_NSS); also elsewhere on the board
/SYSTEM OVERVIEW/MOTOR CONTROL AND IO/DRV_DIAG0: U8.41 (PA8); also elsewhere on the board
/SYSTEM OVERVIEW/MOTOR CONTROL AND IO/DRV_DIAG1: U8.42 (PA9); also elsewhere on the board
/SYSTEM OVERVIEW/MOTOR CONTROL AND IO/DRV_DIR: U8.40 (PC9); also elsewhere on the board
/SYSTEM OVERVIEW/MOTOR CONTROL AND IO/DRV_EN_N: U8.43 (PA10); also elsewhere on the board
/SYSTEM OVERVIEW/MOTOR CONTROL AND IO/DRV_MISO: U8.35 (SPI2_MISO); also elsewhere on the board
/SYSTEM OVERVIEW/MOTOR CONTROL AND IO/DRV_MOSI: U8.36 (SPI2_MOSI); also elsewhere on the board
/SYSTEM OVERVIEW/MOTOR CONTROL AND IO/DRV_SCK: U8.34 (SPI2_SCK); also elsewhere on the board
/SYSTEM OVERVIEW/MOTOR CONTROL AND IO/DRV_STEP: U8.39 (TIM8_CH3); also elsewhere on the board
GND: C18.1, C19.1, C20.2, C21.1, C22.1, C23.1, C24.1, C25.1, C26.1, C27.1, C28.1, C29.2, C30.1, C31.1, C32.1, C33.1, C34.1, C35.1, C36.1, C37.1, D4.3 (common), D5.2 (A2), D6.1 (K), D7.1 (K), J2.A1 (GND), J2.A12 (GND), J2.B1 (GND), J2.B12 (GND), J2.S1 (SHIELD), J3.5 (GND), J3.7 (GND), J4.5 (GND), R26.1, R27.1, R41.1, SW2.1, SW3.1, U6.2 (GND), U7.2 (GND), U8.12 (VSSA), U8.18 (VSS), U8.31 (VSS), U8.47 (VSS), U8.63 (VSS); also elsewhere on the board
unnamed: D6.2 (A), R35.1
unnamed: D7.2 (A), R36.1
VBUS: C21.2, F1.1, J2.A4 (VBUS), J2.A9 (VBUS), J2.B4 (VBUS), J2.B9 (VBUS), U7.5 (VBUS)
VDD: C28.2, C30.2, C31.2, C32.2, C33.2, C34.2, C36.2, FB1.2, NT1.2, U8.1 (VBAT), U8.19 (VDD), U8.32 (VDD), U8.48 (VDDUSB), U8.64 (VDD)
VDDA: C35.2, C37.2, FB1.1, U8.13 (VDDA)

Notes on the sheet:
References:
I2C PULL UPS
Flexible I/O worked examples
AN2867 - Guidelines for oscillator design on STM8AF/AL/S and STM32 MCUs/MPUs
Flexible I/O source configuration
CAN INTERFACE
DESIGN NOTE: blabla
LAYOUT NOTE: blabla
USER INTERFACE
DEBUG INTERFACE
CLOCK SOURCES
DESIGN NOTE: CRYSTAL LOAD CAPACITORS CL = (C1*C2)/(C1+C2) + CS FOR C1 = C2 = C: C = 2*(CL - CS) HSE (Y1): CL = 20 pF CS ≈ 10 pF (MCU + PCB EST.) C24 = C27 ≈ 20 pF USE C0G/NP0 LSE (Y2): CL = 12.5 pF CS ≈ 5 pF (INITIAL EST.) C33 = C34 ≈ 15 pF USE C0G/NP0 VALUES ARE INITIAL DESIGN VALUES. VERIFY/TUNE 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
DESIGN NOTE: 0R LINK FOOTPRINT FOR FUTURE TUNING
MICROCONTROLLER
USB 2.0 INTERFACE
LAYOUT NOTE: AS CLOSE TO μC VDD PINS, ONE PER PIN
